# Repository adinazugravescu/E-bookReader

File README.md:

## Diagrama bloc

##  Bill of Materials (BOM)

| Componenta/Modul                          | Link achizitie                                                                                                                                                                                                                                                                                       | Datasheet                                                                                                                                                             |
|-------------------------------------------|------------------------------------------------------------------------------------------------------------------------------------------------------------------------------------------------------------------------------------------------------------------------------------------------------|-----------------------------------------------------------------------------------------------------------------------------------------------------------------------|
| Buton<br/> (*Model descarcat si adaptat*) | [Buy](https://componentsearchengine.com/prices/TSP1C-RA?manufacturer=KNITTER-SWITCH)                                                                                                                                                                                                                 | [Datasheet](https://docs.rs-online.com/1fd0/0900766b80e2c247.pdf)                                                                                                     |
| Condensator 100nF                         | [Buy](https://ro.mouser.com/ProductDetail/KYOCERA-AVX/04026D104KAT2A?qs=LLG2yGGJ5NhILwMziGI8Xg%3D%3D)                                                                                                                                                                                                | [Datasheet](https://www.mouser.com/catalog/supplier/library/pdf/AVXSurfaceMountCeramic.pdf)                                                                           |
| CPH3225A(C10_SUPERCAP)                    | [Buy](https://ro.mouser.com/ProductDetail/Seiko-Semiconductors/CPH3225A?qs=3etwrb1wR%252BhUOph6lAO7eg%3D%3D)                                                                                                                                                                                         | [Datasheet](https://ro.mouser.com/datasheet/2/360/Seiko_Instruments_MicroBattery_E_20230330_2024Jan_-3561061.pdf)                                                     |
| Condensator 4.7uF                         | [Buy](https://ro.mouser.com/ProductDetail/KEMET/C0402C475M7PACTU?qs=SzIX745sIXFB9Q9KfZhc4g%3D%3D)                                                                                                                                                                                                    | [Datasheet](https://ro.mouser.com/datasheet/2/447/KEM_C1006_X5R_SMD-3316465.pdf)                                                                                      |
| Tantalum Condensator 100uF                | [Buy](https://ro.mouser.com/ProductDetail/KYOCERA-AVX/TAJW107M010RNJ?qs=Wtp%252Bf%2FAeVqIH8v1VxV%252B1Rg%3D%3D)                                                                                                                                                                                      | [Datasheet](https://ro.mouser.com/datasheet/2/40/TAJ-3165264.pdf)                                                                                                     |
| Condensator 1uF                           | [Buy](https://ro.mouser.com/ProductDetail/KYOCERA-AVX/04026D105KAT2A?qs=LLG2yGGJ5NgAzk5fb%252BnzGQ%3D%3D)                                                                                                                                                                                            | [Datasheet](https://ro.mouser.com/datasheet/2/40/cx5r_KGM-3223198.pdf)                                                                                                |
| Condensator 10uF                          | [Buy](https://www.digikey.com/en/products/detail/venkel/C0402X5R100-106MNP/12327194)                                                                                                                                                                                                                 | [Datasheet](https://venkelecd.com/partnumber/datasheet/C0402X5R100-106MNP)                                                                                            |
| CHG_LED                                   | [Buy](https://www.kingbrightusa.com/distyPNInv.asp?sltSearch=distyInv&match=1&txtPartNo=APHM1608ECT)                                                                                                                                                                                                 | [Datasheet](https://www.kingbrightusa.com/images/catalog/SPEC/APHM1608ECT.pdf)                                                                                        |
| USBLC6-2SC6Y                              | [Buy](https://ro.mouser.com/ProductDetail/STMicroelectronics/USBLC6-2SC6Y?qs=gNDSiZmRJS%2FOgDexvXkdow%3D%3D)                                                                                                                                                                                         | [Datasheet](https://ro.mouser.com/datasheet/2/389/usblc6_2sc6y-1852505.pdf)                                                                                           |
| PGB1010603MR                              | [Buy](https://ro.mouser.com/ProductDetail/Littelfuse/PGB1010603MR?qs=gu7KAQ731URLg4GSnNNN7Q%3D%3D)                                                                                                                                                                                                   | [Datasheet](https://www.littelfuse.com/assetdocs/pulseguard-esd-suppressors-pgb1-datasheet?assetguid=8a337998-d54d-466b-be4e-dc5bcd1f9321)                            |
| SD0805S020S1R0                            | [Buy](https://ro.mouser.com/ProductDetail/KYOCERA-AVX/SD0805S020S1R0?qs=jCA%252BPfw4LHbpkAoSnwrdjw%3D%3D)                                                                                                                                                                                            | [Datasheet](https://ro.mouser.com/datasheet/2/40/schottky-3165252.pdf)                                                                                                |
| MBR0530                                   | [Buy](https://ro.mouser.com/ProductDetail/onsemi/MBR0530T1G?qs=3JMERSakeboS%2FFOxJUMWeg%3D%3D)                                                                                                                                                                                                       | [Datasheet](https://www.onsemi.com/download/data-sheet/pdf/mbr0530t1-d.pdf)                                                                                           |
| Condensator 1uF/50V                       | [Buy](https://ro.mouser.com/ProductDetail/KYOCERA-AVX/06035D105MAT2A?qs=k4kUdCzLgS5%252BURKe1SOIeQ%3D%3D)                                                                                                                                                                                            | [Datasheet](https://ro.mouser.com/datasheet/2/40/cx5r_KGM-3223198.pdf)                                                                                                |
| Condensator 0.1uF/50V                     | [Buy](https://ro.mouser.com/ProductDetail/KYOCERA-AVX/04025C104JAT2A?qs=yqaQSyyJnNjAUYBPnTRwrw%3D%3D)                                                                                                                                                                                                | [Datasheet](https://ro.mouser.com/datasheet/2/40/AutoMLCC-2952695.pdf)                                                                                                |
| BD5229G-TR                                | [Buy](https://ro.mouser.com/ProductDetail/ROHM-Semiconductor/BD5229G-TR?qs=4kLU8WoGk0vvnhrrYwdszw%3D%3D)                                                                                                                                                                                             | [Datasheet](https://fscdn.rohm.com/en/products/databook/datasheet/ic/power/voltage_detector/bd52xxg-e.pdf)                                                            |
| XC6220A331MR-G                            | [Buy](https://ro.mouser.com/ProductDetail/Torex-Semiconductor/XC6220A331MR-G?qs=AsjdqWjXhJ8ZSWznL1J0gg%3D%3D)                                                                                                                                                                                        | [Datasheet](https://ro.mouser.com/datasheet/2/760/xc6220-3371556.pdf)                                                                                                 |
| FH34SRJ-24S-0.5SH_99_                     | [Buy](https://ro.mouser.com/ProductDetail/Hirose-Connector/FH34SRJ-24S-0.5SH99?qs=vcbW%252B4%252BSTIpKBl5ap9J8Fw%3D%3D)                                                                                                                                                                              | [Datasheet](https://ro.mouser.com/datasheet/2/185/FH34SRJ_24S_0_5SH_99__CL0580_1255_6_99_2DDrawing_0-1615044.pdf)                                                     |
| USB4110-GF-A                              | [Buy](https://ro.mouser.com/ProductDetail/GCT/USB4110-GF-A?qs=KUoIvG%2F9IlYiZvIXQjyJeA%3D%3D)                                                                                                                                                                                                        | [Datasheet](https://ro.mouser.com/datasheet/2/837/GCT_USB4110_Product_Drawing___20k_cycles-3455479.pdf)                                                               |
| QWIIC_RIGHT_ANGLE                         | [Buy](https://ro.mouser.com/ProductDetail/JST-Commercial/SM04B-SRSS-TBLFSN?qs=cdbOS8ANM9B3FdyA6cNU2A%3D%3D)                                                                                                                                                                                          | [Datasheet](https://ro.mouser.com/datasheet/2/564/eSR_SZ-3476820.pdf)                                                                                                 |
| 112A-TAAR-R03_ATTEND                      | [Buy](https://www.tme.eu/ro/details/mcc-sdmicro/conectori-pentru-cartele/attend/112a-taar-r03/?utm_source=google&utm_medium=cpc&utm_campaign=RUMUNIA%20%5BP%5D%5BDC%5D&gclsrc=aw.ds&gad_source=1&gclid=Cj0KCQjwhr6_BhD4ARIsAH1YdjAAB3boEl8CsGuWhO_BI6GGNh3SIUi2gO3ftspK5-ah9niT38KGMasaAnHZEALw_wcB) | [Datasheet](https://www.attend.com.tw/data/download/file/112A-TAAR-R03.pdf)                                                                                           |
| Bobina                                    | [Buy](https://ro.mouser.com/ProductDetail/Wurth-Elektronik/744043680?qs=PGXP4M47uW6VkZq%252BkzjrHA%3D%3D)                                                                                                                                                                                            | [Datasheet](https://www.we-online.com/components/products/datasheet/744043680.pdf)                                                                                    |
| MCP73831                                  | [Buy](https://ro.mouser.com/ProductDetail/Microchip-Technology/MCP73831T-2ATI-OT?qs=yUQqVecv4qsZbioEUu%252B83g%3D%3D)                                                                                                                                                                                | [Datasheet](https://ro.mouser.com/datasheet/2/268/MCP73831_Family_Data_Sheet_DS20001984H-3441711.pdf)                                                                 |
| PFMF.050.1                                | [Buy](https://ro.mouser.com/ProductDetail/Schurter/PFMF.050.2?qs=1auRipcfynCums5v1iucSA%3D%3D)                                                                                                                                                                                                       | [Datasheet](https://ro.mouser.com/datasheet/2/358/typ_PFMF-1275918.pdf)                                                                                               |
| DMG2305UX-7                               | [Buy](https://ro.mouser.com/ProductDetail/Diodes-Incorporated/DMG2305UX-7?qs=L1DZKBg7t5F%2FNBHrjfxC%252Bg%3D%3D)                                                                                                                                                                                     | [Datasheet](https://www.diodes.com/assets/Datasheets/DMG2305UX.pdf)                                                                                                   |
| SI1308EDL-T1-GE3                          | [Buy](https://ro.mouser.com/ProductDetail/Vishay-Semiconductors/SI1308EDL-T1-GE3?qs=bX1%252BNvsK%2FBramh9tgpOaEw%3D%3D)                                                                                                                                                                              | [Datasheet](https://www.vishay.com/docs/63399/si1308edl.pdf)                                                                                                          |
| Rezistenta 10K                            | [Buy](https://www.digikey.com/en/products/detail/venkel/CR0402-10W-102JT/12332774)                                                                                                                                                                                                                   | [Datasheet](https://data.venkel.com/documents/cr-series?_gl=1*2989pu*_ga*Nzc4NDIxNDY2LjE3NDM3NTUzNDM.*_ga_JRKGBZNVM8*MTc0Mzc1NTM0My4xLjAuMTc0Mzc1NTM0My42MC4wLjA.)    |
| Rezistenta 200                            | [Buy](https://ro.mouser.com/ProductDetail/Vishay-Beyschlag/MCS0402MD2000BE100?qs=3SvaY9RawMJNVte4F12%252BZQ%3D%3D)                                                                                                                                                                                   | [Datasheet](https://www.vishay.com/docs/28952/mcs0402at-mct0603at-mcu0805at-mca1206at.pdf)                                                                            |
| Rezistenta 100K                           | [Buy](https://www.digikey.com/en/products/detail/venkel/CR0402-16W-1003FT/12328296)                                                                                                                                                                                                                  | [Datasheet](https://octopart.com/datasheet/cr0402-16w-1003ft-venkel-16112934)                                                                                         |
| Rezistenta 2.2                            | [Buy](https://www.digikey.com/en/products/detail/venkel/TFCR0402-16W-C-1002BT/12331302)                                                                                                                                                                                                              | [Datasheet](https://data.venkel.com/documents/tfcr-series?_gl=1*1o1n72f*_ga*Nzc4NDIxNDY2LjE3NDM3NTUzNDM.*_ga_JRKGBZNVM8*MTc0Mzc1NTM0My4xLjEuMTc0Mzc1NjA4Mi4yMi4wLjA.) |
| Rezistenta 5K1                            | [Buy](https://ro.mouser.com/ProductDetail/YAGEO/RT0402BRD075K1L?qs=gY0y7AQI9SOxpEAvlEsiTQ%3D%3D)                                                                                                                                                                                                     | [Datasheet](https://ro.mouser.com/datasheet/2/447/PYu_RT_1_to_0_01_RoHS_L_15-3461507.pdf)                                                                             |
| Rezistenta 2K                             | [Buy](https://ro.mouser.com/ProductDetail/Bourns/CR0402AFX-2001GLF?qs=GedFDFLaBXEKjamDtfYtIQ%3D%3D)                                                                                                                                                                                                  | [Datasheet](https://ro.mouser.com/datasheet/2/54/cr_a-1858337.pdf)                                                                                                    |
| Rezistenta 0.47                           | [Buy](https://ro.mouser.com/ProductDetail/Vishay-Beyschlag/MMA02040C4707JB000?qs=YmMt7wOBEV42V6C1Rc7zpg%3D%3D)                                                                                                                                                                                       | [Datasheet](https://www.vishay.com/docs/28713/melfprof.pdf)                                                                                                           |
| Rezistenta 15                             | [Buy](https://ro.mouser.com/ProductDetail/YAGEO/RT0402FRE0715RL?qs=BXCcY9r%252B08DFFpLSkPOIqQ%3D%3D)                                                                                                                                                                                                 | [Datasheet](https://ro.mouser.com/datasheet/2/447/PYu_RT_1_to_0_01_RoHS_L_15-3461507.pdf)                                                                             |
| BME688                                    | [Buy](https://ro.mouser.com/ProductDetail/Bosch-Sensortec/BME688?qs=IS%252B4QmGtzzqQoVDscqwx3A%3D%3D)                                                                                                                                                                                                | [Datasheet](https://ro.mouser.com/datasheet/2/783/bst_bme688_fl000-2307034.pdf)                                                                                       |
| W25Q512JVEIQ                              | [Buy](https://ro.mouser.com/ProductDetail/Winbond/W25Q512JVEIQ?qs=l7cgNqFNU1jw6svr3at6tA%3D%3D)                                                                                                                                                                                                      | [Datasheet](https://ro.mouser.com/datasheet/2/949/Winbond_W25Q512JV_Datasheet-3240039.pdf)                                                                            |
| ESP32-C6-WROOM-1-N8                       | [Buy](https://ro.mouser.com/ProductDetail/Espressif-Systems/ESP32-C6-WROOM-1-N8?qs=8Wlm6%252BaMh8ST02Gmwp74cw%3D%3D)                                                                                                                                                                                 | [Datasheet](https://ro.mouser.com/datasheet/2/891/Espressif_ESP32_C6_WROOM_1__Datasheet_V0_1_PRELIMI-3239987.pdf)                                                     |
| DS3231SN#                                 | [Buy](https://ro.mouser.com/ProductDetail/Analog-Devices-Maxim-Integrated/DS3231SN?qs=1eQvB6Dk1vhUlr8%2FOrV0Fw%3D%3D)                                                                                                                                                                                | [Datasheet](https://ro.mouser.com/datasheet/2/609/DS3231-3421123.pdf)                                                                                                 |
| MAX17048G+T10                             | [Buy](https://ro.mouser.com/ProductDetail/Analog-Devices-Maxim-Integrated/MAX17048G%2bT10?qs=D7PJwyCwLAoGnnn8jEPRBQ%3D%3D)                                                                                                                                                                           | [Datasheet](https://ro.mouser.com/datasheet/2/609/MAX17048_MAX17049-3469099.pdf)                                                                                      |
| Solder Jumper                             | [Buy](https://ro.mouser.com/ProductDetail/Vishay-Dale/CRCW04020000Z0EEHP?qs=sGAEpiMZZMtlubZbdhIBIKF%2FTFcY2hSpgvMg4uB1QYw%3D)                                                                                                                                                                        | [Datasheet](https://www.vishay.com/docs/20043/crcwhpe3.pdf)                                                                                                           |
| Test Pad                                  | [Buy](https://www.digikey.com/en/products/detail/keystone-electronics/5006/255330)                                                                                                                                                                                                                   | [Datasheet](https://www.keyelco.com/userAssets/file/M65p56.pdf)                                                                                                       |
##  Descriere functionalitate hardware

Proiectul este bazat pe un microcontroller **ESP32-C6-WROOM-1-N8**, alimentat printr-un LDO 3V3 dintr-o baterie Li-Po(1800 mAh). Alimentarea este gestionata de un circuit de incarcare **MCP73831** conectat la USB-C. ESP32-C6-WROOM-1-N8 controleaza toate componentele externe prin interfete standard SPI, I2C si GPIO:

- **E-paper Display** – conectat prin **SPI**
- **SD Card** – **SPI**, pentru stocare
- **NOR Flash** – **SPI**, memorie externa
- **RTC DS3231SN#** – conectat prin **I2C** pentru ceas de timp real
- **SENSOR2 BME688** – senzor de mediu conectat pe aceeasi magistrala **I2C**
- **RESET&BOOT/IO** – conectate prin GPIO
- **Qwiic/Stemma QT** – extensie I2C pentru senzori/modul aditionali
- **Test Pads** – pentru TX/RX UART + debugging hardware

Comunicarea cu display-ul si stocarea se face prin interfete rapide SPI. Toate componentele I2C partajeaza linia SDA si SCL, pentru a minimiza utilizarea pinilor.

**Specificatii electronice componente principale**

   - Microcontroller – ESP32-C6-WROOM-1-N8 CPU: 32-bit RISC-V single-core, frecventa maxima 160 MHz. Memorie interna: 320KB ROM, 512KB HP SRAM, 16KB LP SRAM. Conectivitate: Wi-Fi 6 si Bluetooth LE 5.0. Tensiune de operare: 3.3V. Consum de curent: 160–260 mA in mod activ, 3–20 mA in modem-sleep, 0.8 mA in light-sleep, 10 µA in deep-sleep, 2.5 µA in hibernare.

   - Display – E-paper 7.5": Display de tip ePaper, ales pentru consumul extrem de redus si lizibilitatea foarte buna in lumina naturala.

   - Memorie: Stocarea este realizata cu un card MicroSD si un cip NOR Flash de 64MB conectat pe aceeasi magistrala SPI.

   - Senzor ambiental – BME688: Senzor digital care masoara temperatura, umiditatea, presiunea si compozitia gazelor.Tensiune de alimentare: 1.71V – 3.6V. Consum: <1 mA in mod activ, <1 µA in mod sleep.

   - Regulator tensiune – XC6220A331MR-G: LDO pentru conversia tensiunii bateriei la 3.3V. Curent maxim de iesire: 700 mA. Tensiune de cadere: aprox. 250 mV la 500 mA.

   - Circuit incarcare baterie – MCP73831: Controller linear pentru incarcare acumulatori Li-Po. Tensiune intrare: 3.75V – 6V. Curent maxim programabil pana la 500 mA.

##  Utilizarea pinilor ESP32-C6

| Componenta         | Pin ESP32-C6 | Functie     | Justificare                                                  |
|--------------------|--------------|-------------|--------------------------------------------------------------|
| **EPD**            | IO7          | MOSI        | Pin dedicat SPI pentru date, permite viteza mare de transfer |
|                    | IO6          | SCK         | Clock SPI standard                                           |
|                    | IO10         | EPD_CS      | Linie de selectare pentru e-paper                            |
|                    | IO5          | EPD_DC      | Selecteaza intre comanda si date trimise                     |
|                    | IO3          | EPD_BUSY    | Citire stare de ocupare a display-ului                       |
|                    | IO23         | EPD_RST     | Reset hardware                                               |
| **SD Card**        | IO6          | SCK         | Linie separata CS pentru SD card                             |
|                    | IO2          | MISO        | Linie unica pentru citirea datelor                           |
|                    | IO7          | MOSI        | Linie partajata de scriere                                   |
|                    | IO4          | SS_SD       | Linie de chip select pentru SD card                          |
| **NOR Flash**      | IO2          | MISO        | Linie CS separata pentru memoria Flash                       |
|                    | IO7          | MOSI        | Linie partajata de scriere                                   |
|                    | IO11         | FLASH_CS    | Selectare separata a chipului de memorie                     |
|                    | IO6          | SCK         | Clock SPI comun                                              |
| **RTC DS3231SN**   | IO21         | SDA         | Linie I2C standard pentru date                               |
|                    | IO22         | SCL         | Linie I2C standard pentru ceas                               |
|                    | IO18         | RTC_RST     | Reset software controlabil pentru RTC                        |
|                    | IO0          | INT_RTC     | Wake-up de la RTC                                            |
|                    | IO1          | 32KHZ       | Iesire frecventa                                             |
| **BME688**         | IO21         | SDA         | I2C partajat                                                 |
|                    | IO22         | SCL         | I2C partajat                                                 |
|                    | IO19         | I2C_PW      | Control alimentare senzor                                    |
| **Qwiic**          | IO21 / IO22  | SDA/SCL     | ~                                                            |
| **E-paper Power**  | IO20         | EPD_3V3_C   | Activeaza alimentarea prin tranzistor                        |
| **BOOT Button**    | IO9          | IO/BOOT     | Pin standard pentru intrare in modul flash                   |
| **CHANGE Button**  | IO15         | IO/CHANGE   | Permite comutarea intre modurile de functionare              |
| **RESET Button**   | EN           | RESET       | Pin hardware de reset (activ LOW)                            |
| **UART Debug**     | GPIO16       | TX (TXD0)   | Pentru debug/programare                                      |
|                    | GPIO17       | RX (RXD0)   | Pentru debug/programare                                      |
| **USB**            | IO12, IO13   | USB D- / D+ | Comunicare USB-C                                             |

---
## Etapele implementarii proiectului

1. **Realizarea schematicului**  
   Am creat schema electrica pe baza modelului oferit, utilizand componentele si simbolurile din biblioteca furnizata. Am avut grija sa respect toate cerintele tehnice si sa evit erorile de ERC. Avertismentele ramase au fost acceptate, deoarece reies direct din structura impusa de model.

2. **Proiectarea PCB-ului**  
   Am trecut in modul PCB, unde am plasat toate componentele pe stratul top, conform pozitiei si dimensiunilor impuse. Am decupat antena modulului ESP32-C6 si am pozitionat corect toate elementele, astfel incat sa incapa in carcasa.

3. **Rutarea si planul de masa**  
   Am realizat rutarea pe baza constrangerilor din tema, am aplicat plan de masa atat pe stratul top, cat si pe stratul bottom, si am adaugat via stitching intre cele doua straturi pentru integritate electrica .

4. **Adaugarea informatiilor de productie**  
   Am etichetat toate componentele pe silkscreen pentru o vizualizare clara in 3D si pentru productie.

5. **Integrarea modelelor 3D**  
   Am importat modelele 3D corespunzatoare pentru fiecare componenta in parte si le-am creat modelele 3D.

6. **Modelarea carcasei**  
   Am adaptat carcasa astfel incat placa sa se potriveasca perfect in interior, respectand cerintele mecanice de montaj.

7. **Constructia componentelor externe**  
   Am construit modelul 3D al bateriei si al display-ului conform dimensiunilor si detaliilor din datasheet-urile oferite.

###  Probleme intampinate

- Gasirea unui model 3D compatibil cu footprint-ul butonului a fost dificila, asa ca am modificat manual un model descarcat.
- In schematic, anumite warning-uri au fost acceptate deoarece erau implicite in structura designului cerut.
- Au fost acceptate cele doua erori DRC aparute la mufa USB, conform instructiunilor primite.

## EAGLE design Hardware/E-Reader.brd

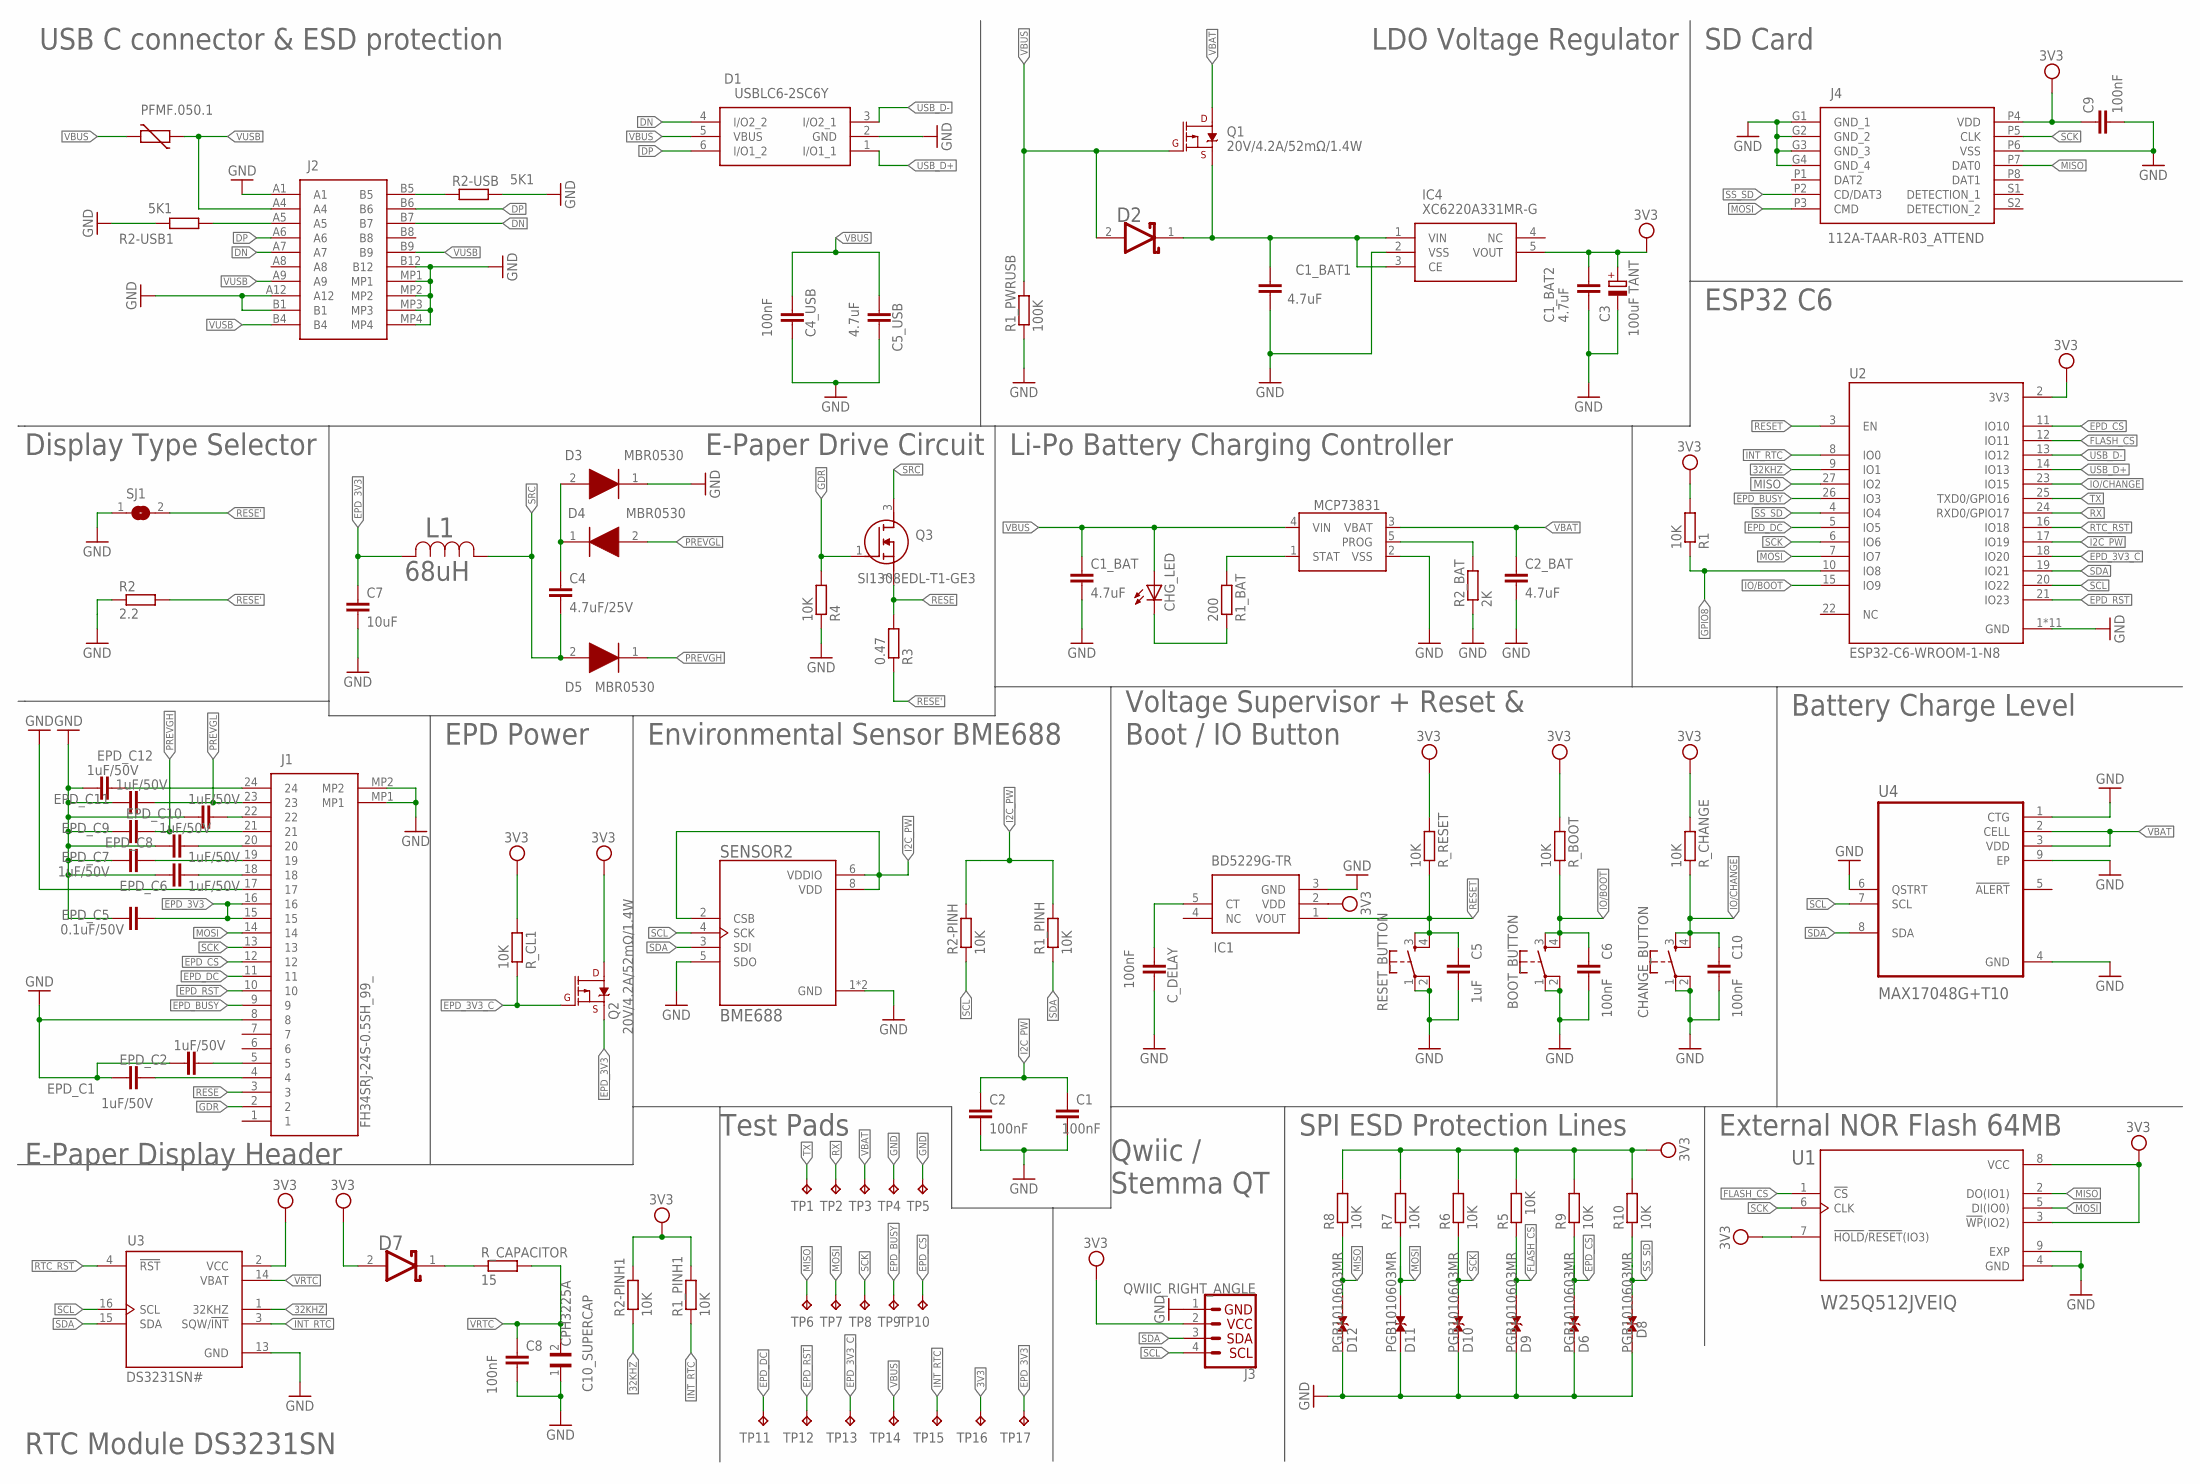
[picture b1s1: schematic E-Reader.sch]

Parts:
BOOT_BUTTON: BUTTON_CUSYOMV1; MYBUTTON
C1, C2, C4_USB, C6, C8, C9, C10: 100nF; EAGLE-LTSPICE_C0402
C1_BAT, C1_BAT1, C1_BAT2, C2_BAT, C5_USB: 4.7uF; EAGLE-LTSPICE_C0402
C3: 100uF TANT; RCL_CT3528
C4: 4.7uF/25V; EAGLE-LTSPICE_C0402
C5: 1uF; EAGLE-LTSPICE_C0402
C7: 10uF; EAGLE-LTSPICE_C0402
C10_SUPERCAP: CPH3225A; CAPCP3225X100N
CHANGE_BUTTON: BUTTON_CUSYOMV1; MYBUTTON
CHG_LED: ADAFRUIT_LEDCHIP-LED0603; ADAFRUIT_CHIP-LED0603
C_DELAY: 100nF; EAGLE-LTSPICE_C0402
D1: USBLC6-2SC6Y; SOT95P280X145-6N
D2, D7: ESP32_WROVER_AVX---SD0805S020S1R0_AVX_SD0805S020S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; ESP32_WROVER_AVX---SD0805S020S1R0_AVX_SD0805S020S1R0_0
D3, D4, D5: MBR0530; SOD3716X135N
D6, D8, D9, D10, D11, D12: PGB1010603MR; DIOC1608X36N
EPD_C1, EPD_C2, EPD_C6, EPD_C7, EPD_C8, EPD_C9, EPD_C10, EPD_C11, EPD_C12: 1uF/50V; EAGLE-LTSPICE_C0402
EPD_C5: 0.1uF/50V; EAGLE-LTSPICE_C0402
IC1: BD5229G-TR; SOT95P280X125-5N
IC4: XC6220A331MR-G; SOT95P280X120-5N
J1: FH34SRJ-24S-0.5SH_99_; FH34SRJ24S05SH99
J2: SAMACSYS_PARTS_USB4110-GF-A; SAMACSYS_PARTS_USB4110GFA
J3: QWIIC_RIGHT_ANGLE; JST04_1MM_RA
J4: 112A-TAAR-R03_ATTEND; 112ATAARR03ATTEND
L1: 68uH; IND_4828-WE-TPC_WRE
MCP73831: ESP32_WROVER_SPARKFUN-IC-POWER_MCP73831; ESP32_WROVER_SPARKFUN-IC-POWER_SOT23-5
PFMF.050.1: ESP32C6_VARISTORCN1812; ESP32C6_VARISTOR_CT/CN1812
Q1, Q2: 20V/4.2A/52mΩ/1.4W; ESP32_WROVER_SPARKFUN-DISCRETESEMI_SOT23-3
Q3: SI1308EDL-T1-GE3; SOT65P210X110-3N
R1, R1_PINH, R1_PINH1, R2-PINH, R2-PINH1, R4, R5, R6, R7, R8, R9, R10: 10K; ESP32_WROVER_EAGLE-LTSPICE_R0402
R1_BAT: 200; ESP32_WROVER_EAGLE-LTSPICE_R0402
R1_PWRUSB: 100K; ESP32_WROVER_EAGLE-LTSPICE_R0402
R2: 2.2; ESP32_WROVER_EAGLE-LTSPICE_R0402
R2-USB, R2-USB1: 5K1; ESP32_WROVER_EAGLE-LTSPICE_R0402
R2_BAT: 2K; ESP32_WROVER_EAGLE-LTSPICE_R0402
R3: 0.47; ESP32_WROVER_EAGLE-LTSPICE_R0402
RESET_BUTTON: BUTTON_CUSYOMV1; MYBUTTON
R_BOOT: 10K; ESP32_WROVER_EAGLE-LTSPICE_R0402
R_CAPACITOR: 15; ESP32_WROVER_EAGLE-LTSPICE_R0402
R_CHANGE: 10K; ESP32_WROVER_EAGLE-LTSPICE_R0402
R_CL1: 10K; ESP32_WROVER_EAGLE-LTSPICE_R0402
R_RESET: 10K; ESP32_WROVER_EAGLE-LTSPICE_R0402
SENSOR2: BME688; ESP32_WROVER_BME680_PSON80P300X300X100-8N
SJ1: SJ
TP1, TP2, TP3, TP4, TP5, TP6, TP7, TP8, TP9, TP10, TP11, TP12, TP13, TP14, TP15, TP16, TP17: TPTP20R; TP20R
U1: W25Q512JVEIQ; SON127P600X800X80-9N
U2: ESP32-C6-WROOM-1-N8; XCVR_ESP32-C6-WROOM-1-N8
U3: DS3231SN#; SOIC127P1032X265-16N
U4: MAX17048G+T10; SON50P200X200X80-9N

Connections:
3V3: C1_BAT2.1, C3.+, C9.1, D7.2 (ANODE), IC1.2 (VDD), IC4.5 (VOUT), J3.2, J4.P4 (VDD), Q2.3 (D), R1.2, R1_PINH1.2, R2-PINH1.2, R5.2, R6.2, R7.2, R8.2, R9.2, R10.2, R_BOOT.2, R_CHANGE.2, R_CL1.2, R_RESET.2, TP16.TP, U1.3 (!WP!(IO2)), U1.7 (!HOLD!/!RESET!(IO3)), U1.8 (VCC), U2.2 (3V3), U3.2 (VCC)
32KHZ: R2-PINH1.1, U2.9 (IO1), U3.1 (32KHZ)
DN: D1.4 (I/O2_2), J2.A7, J2.B7
DP: D1.6 (I/O1_2), J2.A6, J2.B6
EPD_3V3: C7.1, EPD_C5.2, J1.15, J1.16, L1.2, Q2.2 (S), TP17.TP
EPD_3V3_C: Q2.1 (G), R_CL1.1, TP13.TP, U2.18 (IO20)
EPD_BUSY: J1.9, TP9.TP, U2.26 (IO3)
EPD_CS: D6.2, J1.12, R9.1, TP10.TP, U2.11 (IO10)
EPD_DC: J1.11, TP11.TP, U2.5 (IO5)
EPD_RST: J1.10, TP12.TP, U2.21 (IO23)
FLASH_CS: D9.2, R5.1, U1.1 (!CS), U2.12 (IO11)
GDR: J1.2, Q3.1 (G), R4.2
GND: BOOT_BUTTON.1, BOOT_BUTTON.2, C1.2, C1_BAT.2, C1_BAT1.2, C1_BAT2.2, C2.2, C2_BAT.2, C3.-, C4_USB.2, C5.2, C5_USB.2, C6.2, C7.2, C8.2, C9.2, C10.2, C10_SUPERCAP.1, CHANGE_BUTTON.1, CHANGE_BUTTON.2, C_DELAY.2, D1.2 (GND), D3.1 (K), D6.1, D8.1, D9.1, D10.1, D11.1, D12.1, EPD_C1.1, EPD_C2.1, EPD_C5.1, EPD_C6.1, EPD_C7.1, EPD_C8.1, EPD_C9.1, EPD_C10.1, EPD_C11.1, EPD_C12.1, IC1.3 (GND), IC4.2 (VSS), J1.8, J1.17, J1.MP1, J1.MP2, J2.A1, J2.A12, J2.B1, J2.B12, J2.MP1, J2.MP2, J2.MP3, J2.MP4, J3.1, J4.G1 (GND_1), J4.G2 (GND_2), J4.G3 (GND_3), J4.G4 (GND_4), J4.P6 (VSS), MCP73831.2 (VSS), R1_PWRUSB.1, R2.1, R2-USB.2, R2-USB1.1, R2_BAT.1, R4.1, RESET_BUTTON.1, RESET_BUTTON.2, SENSOR2.1 (GND), SENSOR2.5 (SDO), SENSOR2.7 (GND), SJ1.1, TP4.TP, TP5.TP, U1.4 (GND), U1.9 (EXP), U2.1 (GND), U2.28 (GND), U2.29_1 (GND), U2.29_2 (GND), U2.29_3 (GND), U2.29_4 (GND), U2.29_5 (GND), U2.29_6 (GND), U2.29_7 (GND), U2.29_8 (GND), U2.29_9 (GND), U3.13 (GND), U4.1 (CTG), U4.4 (GND), U4.6 (QSTRT), U4.9 (EP)
GPIO8: R1.1, U2.10 (IO8)
I2C_PW: C1.1, C2.1, R1_PINH.2, R2-PINH.2, SENSOR2.2 (CSB), SENSOR2.6 (VDDIO), SENSOR2.8 (VDD), U2.17 (IO19)
INT_RTC: R1_PINH1.1, TP15.TP, U2.8 (IO0), U3.3 (SQW/!INT)
IO/BOOT: BOOT_BUTTON.3, BOOT_BUTTON.4, C6.1, R_BOOT.1, U2.15 (IO9)
IO/CHANGE: C10.1, CHANGE_BUTTON.3, CHANGE_BUTTON.4, R_CHANGE.1, U2.23 (IO15)
MISO: D12.2, J4.P7 (DAT0), R8.1, TP6.TP, U1.2 (DO(IO1)), U2.27 (IO2)
MOSI: D11.2, J1.14, J4.P3 (CMD), R7.1, TP7.TP, U1.5 (DI(IO0)), U2.7 (IO7)
unnamed: C1_BAT1.1, D2.1 (CATHODE), IC4.1 (VIN), IC4.3 (CE), Q1.2 (S)
unnamed: MCP73831.5 (PROG), R2_BAT.2
unnamed: MCP73831.1 (STAT), R1_BAT.2
unnamed: CHG_LED.C, R1_BAT.1
unnamed: C_DELAY.1, IC1.5 (CT)
unnamed: EPD_C6.2, J1.18
unnamed: C4.1, D3.2 (A), D4.1 (K)
unnamed: EPD_C7.2, J1.19
unnamed: EPD_C1.2, J1.4
unnamed: EPD_C2.2, J1.5
unnamed: D7.1 (CATHODE), R_CAPACITOR.1
unnamed: EPD_C8.2, J1.20
unnamed: J2.B5, R2-USB.1
unnamed: EPD_C10.2, J1.22
unnamed: J2.A5, R2-USB1.2
unnamed: EPD_C12.2, J1.24
PREVGH: D5.1 (K), EPD_C9.2, J1.21
PREVGL: D4.2 (A), EPD_C11.2, J1.23
RESE: J1.3, Q3.2 (S), R3.2
RESE': R2.2, R3.1, SJ1.2
RESET: C5.1, IC1.1 (VOUT), RESET_BUTTON.3, RESET_BUTTON.4, R_RESET.1, U2.3 (EN)
RTC_RST: U2.16 (IO18), U3.4 (!RST)
RX: TP2.TP, U2.24 (RXD0/GPIO17)
SCK: D10.2, J1.13, J4.P5 (CLK), R6.1, TP8.TP, U1.6 (CLK), U2.6 (IO6)
SCL: J3.4, R2-PINH.1, SENSOR2.4 (SCK), U2.20 (IO22), U3.16 (SCL), U4.7 (SCL)
SDA: J3.3, R1_PINH.1, SENSOR2.3 (SDI), U2.19 (IO21), U3.15 (SDA), U4.8 (SDA)
SRC: C4.2, D5.2 (A), L1.1, Q3.3 (D)
SS_SD: D8.2, J4.P2 (CD/DAT3), R10.1, U2.4 (IO4)
TX: TP1.TP, U2.25 (TXD0/GPIO16)
USB_D+: D1.1 (I/O1_1), U2.14 (IO13)
USB_D-: D1.3 (I/O2_1), U2.13 (IO12)
VBAT: C2_BAT.1, MCP73831.3 (VBAT), Q1.3 (D), TP3.TP, U4.2 (CELL), U4.3 (VDD)
VBUS: C1_BAT.1, C4_USB.1, C5_USB.1, CHG_LED.A, D1.5 (VBUS), D2.2 (ANODE), MCP73831.4 (VIN), PFMF.050.1.2, Q1.1 (G), R1_PWRUSB.2, TP14.TP
VRTC: C8.1, C10_SUPERCAP.2, R_CAPACITOR.2, U3.14 (VBAT)
VUSB: J2.A4, J2.A9, J2.B4, J2.B9, PFMF.050.1.1

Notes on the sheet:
USB C connector & ESD protection
LDO Voltage Regulator
SD Card
ESP32 C6
Li-Po Battery Charging Controller
E-Paper Drive Circuit
Display Type Selector
E-Paper Display Header
EPD Power
Environmental Sensor BME688
Voltage Supervisor + Reset & Boot / IO Button
Battery Charge Level
External NOR Flash 64MB
SPI ESD Protection Lines
Qwiic / Stemma QT
Test Pads
RTC Module DS3231SN

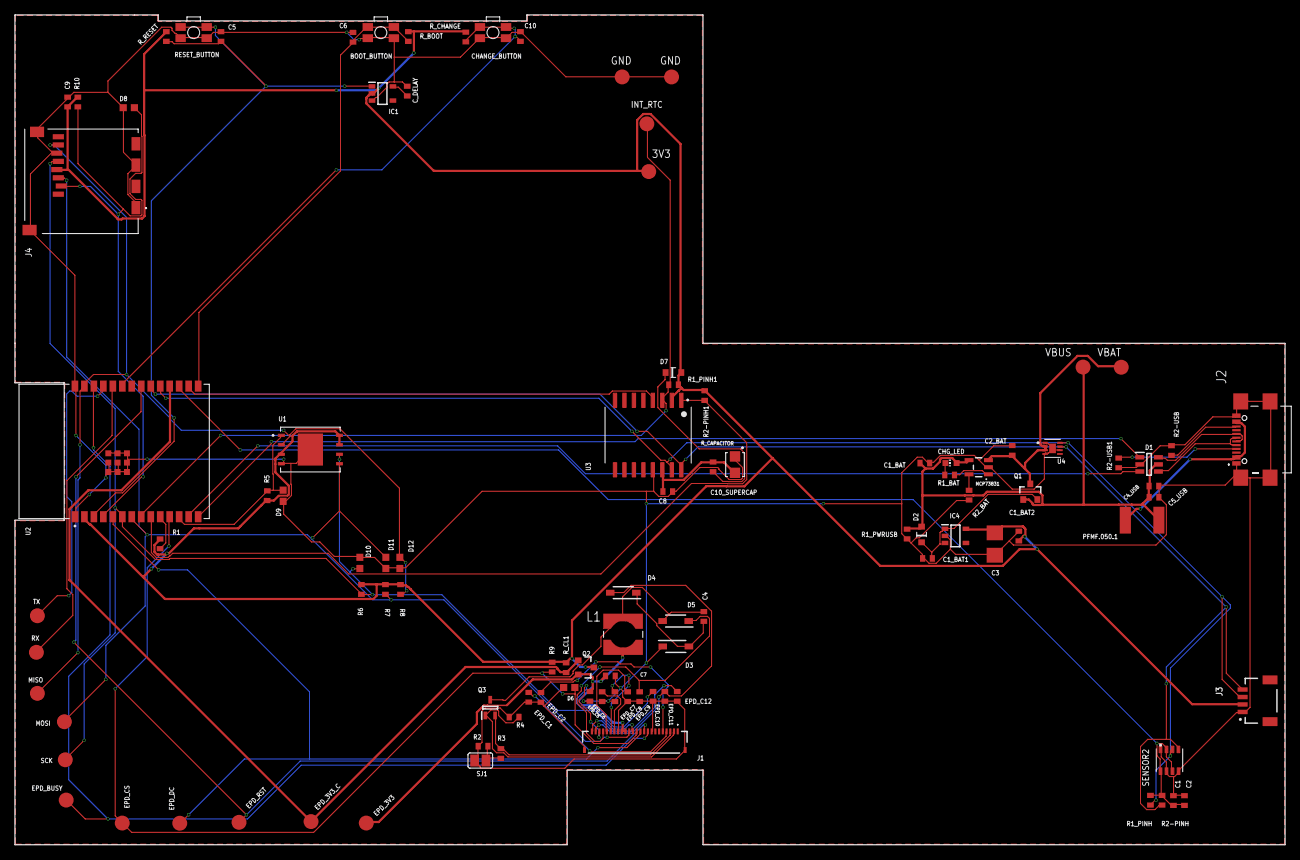
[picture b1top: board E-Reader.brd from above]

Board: 2 copper layers, 170.2 x 111.2 mm, 103 parts (0 on the bottom side), 55 nets.

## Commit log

2025-04-03 Create LICENSE
2025-04-12 add .f3z

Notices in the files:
parts and their libraries:
COPYRIGHT: Copyright (C) 2024 Ultra Librarian. All rights reserved.
